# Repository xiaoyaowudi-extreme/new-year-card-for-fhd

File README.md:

This project contains the design of the pcb which will be sent to fhd on the Valentine's Day.

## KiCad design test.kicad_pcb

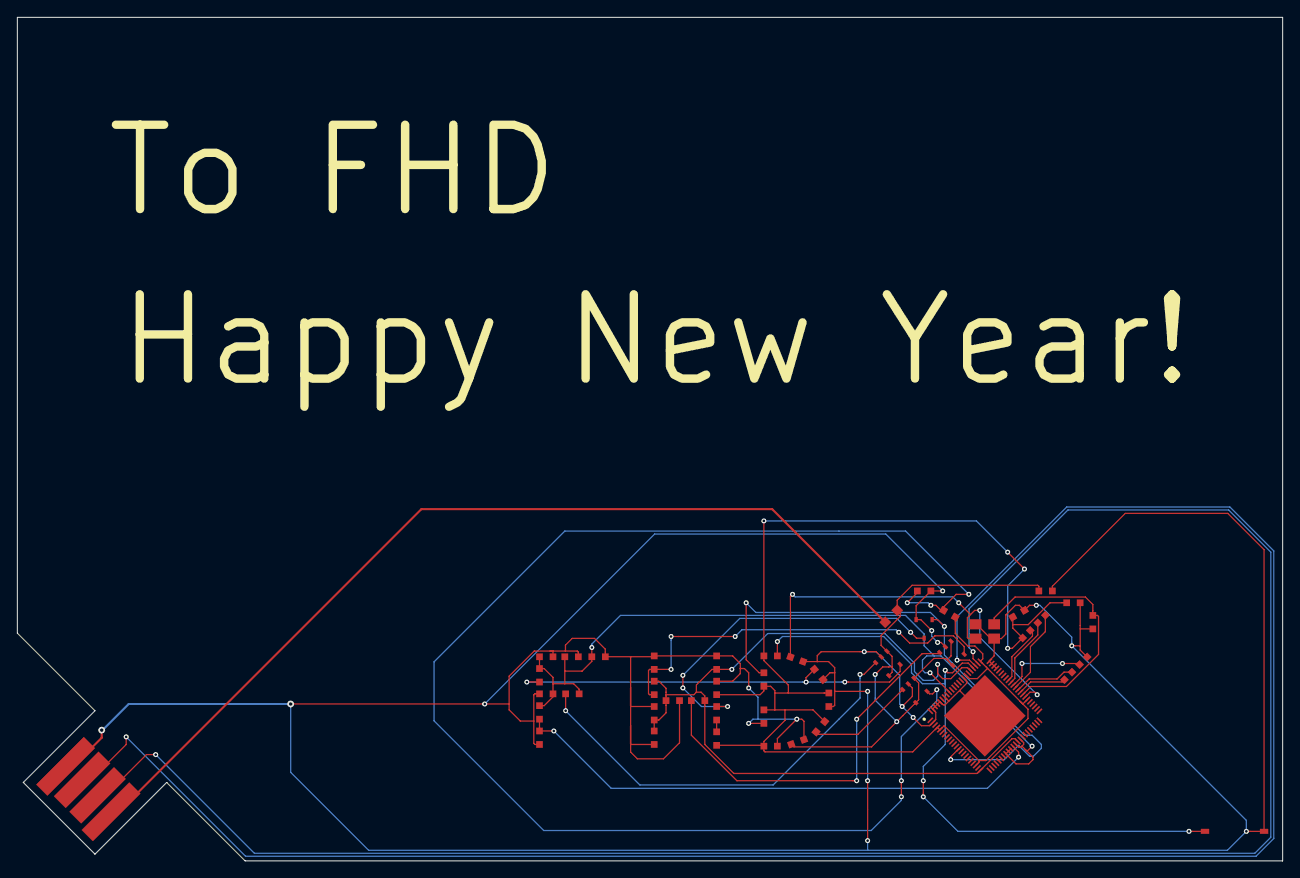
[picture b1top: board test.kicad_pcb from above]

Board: 2 copper layers, 150.0 x 100.0 mm, 43 parts (0 on the bottom side), 27 nets.

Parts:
C1, C4, C5: 22u; 0603
C2, C3, C14: 2u2; 0603
C6, C7: 1u; 0603
C8, C9: 30p; 0603
C10, C11, C12, C13, C15, C16, C17, C18: 100n; 0603
D1: LED; 0603
F1: Polyfuse; 0805
IC1: F1C100S; QFN40P1000X1000X90-89N-D
J1: USB_B; usb-PCB
L1, L2, L3: 2u2; 0603
Q1: Q_NMOS_GSD; nmos
R1, R3: 11k; 0603
R2: 36k; 0603
R4: 10k; 0603
R5, R10, R11: 49k9; 0603
R6: 8k2; 0603
R7, R8: 2k2; 0603
R9: R; 0603
SW1: SW_Push; button
U1, U3, U4: JW5211
U2: CSNP1GCR01
Y1: 24MHz; crystal

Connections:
+1V1: C5.1, C10.1, C11.1, C12.1, IC1.22, IC1.35, IC1.71, L3.2, R6.2
+2V5: C1.1, C6.1, C7.1, C13.2, IC1.30, IC1.31, IC1.32, IC1.34, IC1.36, IC1.80, L1.2, R2.2, R7.1
+3V3: C4.1, C14.1, C15.1, C16.1, C17.1, C18.1, D1.2, IC1.4, IC1.5, IC1.20, IC1.50, IC1.67, IC1.73, L2.2, R5.2, R10.1, R11.1, U2.8
/CLKN: C9.1, IC1.51, Y1.1
/CLKP: C8.1, IC1.52, Y1.3
/FUSE_PWR: C2.1, C3.1, F1.2, U1.1, U1.4, U3.1, U3.4, U4.1, U4.4
/RESET: IC1.70, R11.2, SW1.1
/SDC0_CLK: IC1.56, U2.3
/SDC0_CMD: IC1.55, U2.5
/SDC0_DAT0: IC1.57, U2.6
/SDC0_DAT1: IC1.58, U2.7
/SDC0_DAT2: IC1.53, U2.1
/SDC0_DAT3: IC1.54, U2.2
/STATUS: IC1.13, Q1.1, R10.2
/SVREF: IC1.33, R7.2, R8.1
/USB_DM: IC1.68, J1.2
/USB_DP: IC1.69, J1.3
GND: C1.2, C2.2, C3.2, C4.2, C5.2, C6.2, C7.2, C8.2, C9.2, C10.2, C11.2, C12.2, C13.1, C14.2, C15.2, C16.2, C17.2, C18.2, IC1.2, IC1.63, IC1.64, IC1.65, IC1.66, IC1.74, IC1.82, IC1.84, IC1.85, IC1.86, IC1.87, IC1.89, J1.4, Q1.2, R1.2, R3.2, R4.2, R8.2, SW1.2, U1.2, U2.4, U3.2, U4.2, Y1.2, Y1.4
unnamed: D1.1, R9.1
unnamed: F1.1, J1.1
unnamed: L1.1, U1.3
unnamed: L2.1, U3.3
unnamed: L3.1, U4.3
unnamed: Q1.3, R9.2
unnamed: R1.1, R2.1, U1.5
unnamed: R3.1, R5.1, U3.5
unnamed: R4.1, R6.1, U4.5

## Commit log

2020-01-12 add pcb file
2020-01-12 add contributor and README
